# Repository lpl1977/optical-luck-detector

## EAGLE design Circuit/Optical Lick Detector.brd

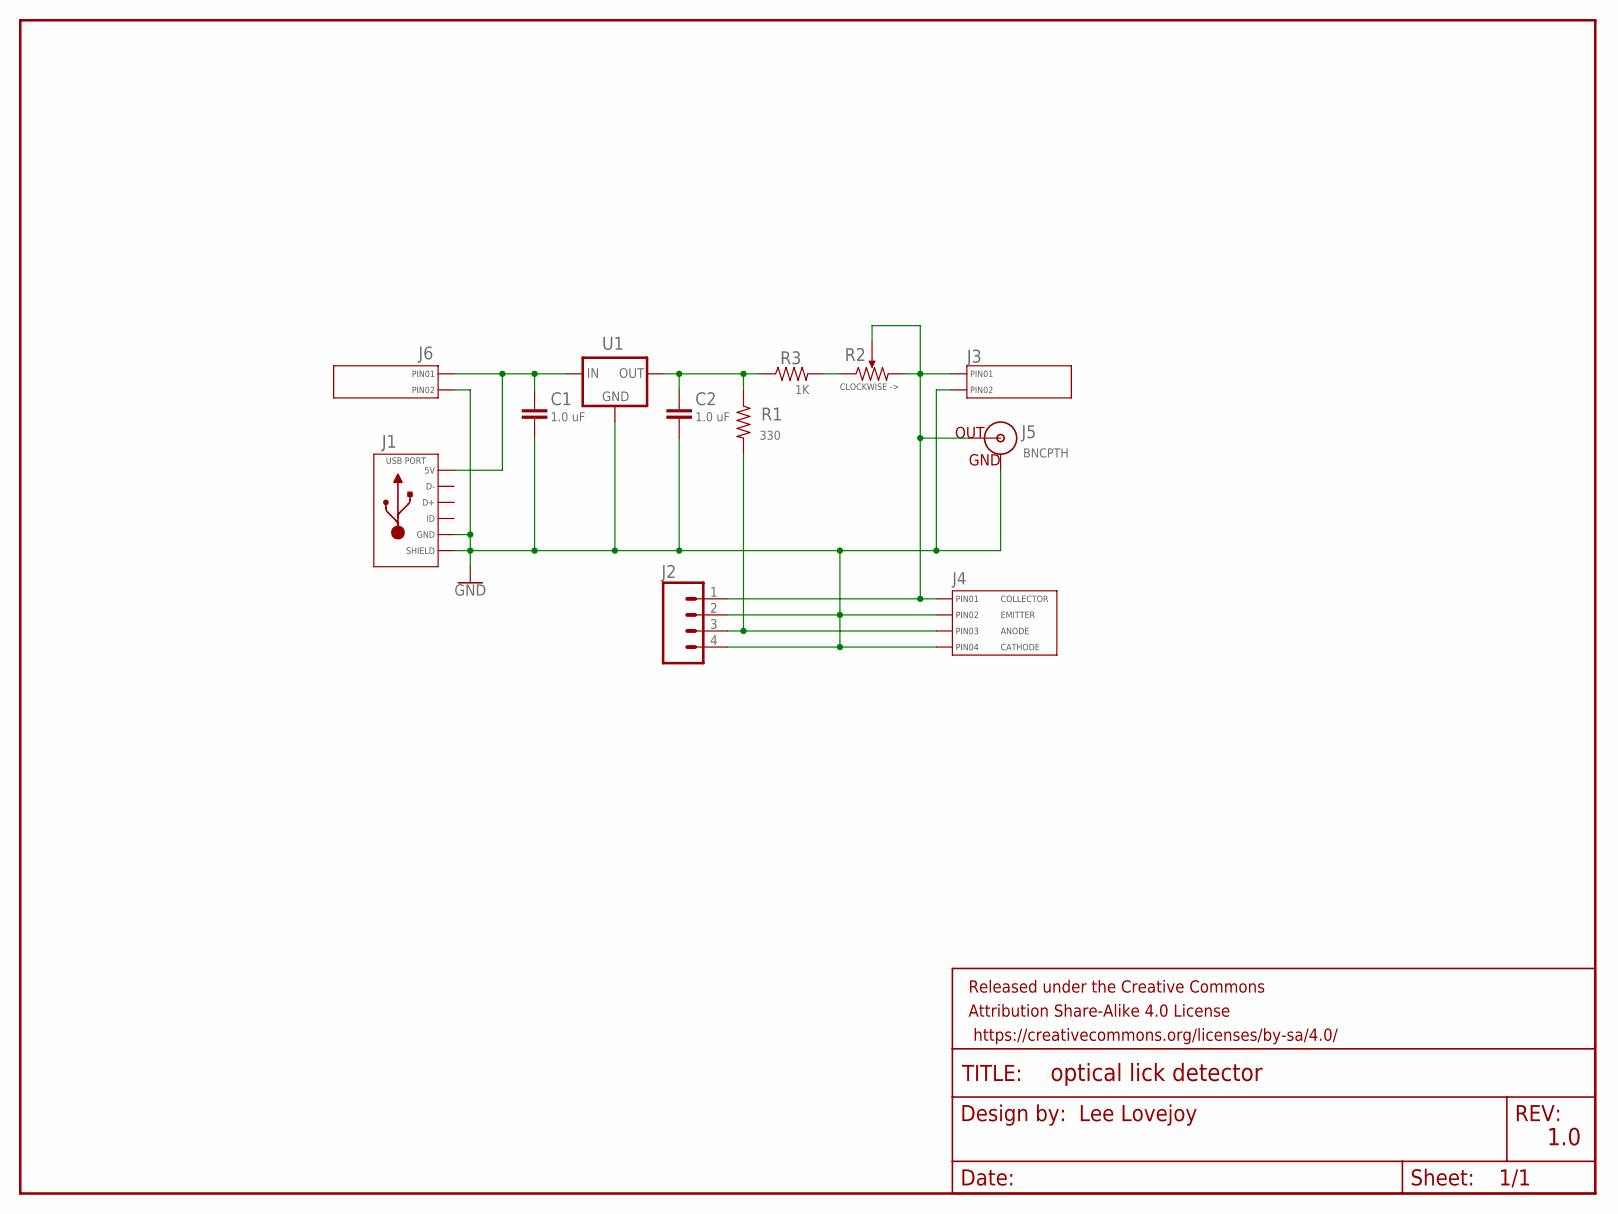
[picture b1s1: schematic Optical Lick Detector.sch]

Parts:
C1, C2: 1.0 uF; C0603
FRAME1: FRAME-LETTER; CREATIVE_COMMONS
J1: MF-CON-MICROUSB-RIGHT; MICROUSB-RIGHT
J2: CONN_041X04_NO_SILK; 1X04_NO_SILK
J3, J6: CONN_023.5MM; SCREWTERMINAL-3.5MM-2
J4: CONN_04SCREW; SCREWTERMINAL-3.5MM-4
J5: BNCPTH; BNC
R1: 330; R0402
R2: MF-RES-TC33X-10K; TC33
R3: 1K; R0402
U1: MIC5200; SOT223

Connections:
ANODE: J2.3, J4.3 (PIN3), R1.P$2
COLLECTOR: J2.1, J3.1 (PIN1), J4.1 (PIN1), J5.S (OUT), R2.P$2, R2.P$3
GND: C1.P$2 (2), C2.P$2 (2), J1.5 (GND), J1.S1 (SLD), J1.S2 (SLD), J1.S3 (SLD), J1.S4 (SLD), J1.S5 (SLD), J1.S6 (SLD), J2.2, J2.4, J3.2 (PIN2), J4.2 (PIN2), J4.4 (PIN4), J5.GND, J6.2 (PIN2), U1.2 (GND), U1.4 (GND)
unnamed: C1.P$1 (1), J1.1 (5V), J6.1 (PIN1), U1.1 (IN)
unnamed: C2.P$1 (1), R1.P$1, R3.P$1, U1.3 (OUT)
unnamed: R2.P$1, R3.P$2

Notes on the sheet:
1.0

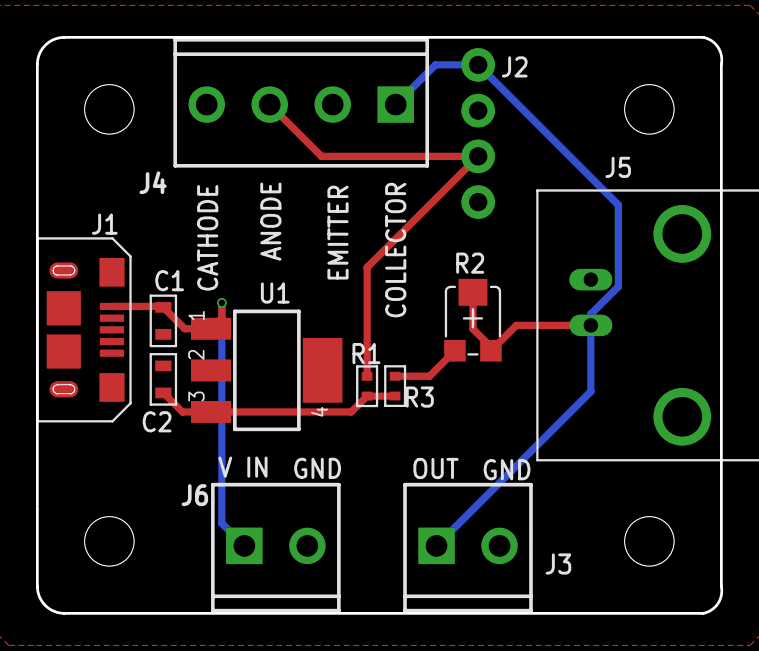
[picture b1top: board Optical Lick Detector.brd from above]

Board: 2 copper layers, 38.0 x 32.0 mm, 13 parts (0 on the bottom side), 6 nets.

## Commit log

2019-05-03 Schematics and board files for optical lick detector
    EAGLE schematics and board files for optical lick detector.
2019-05-17 Rearrange files
    Create separate folders for physical and circuit schematics
2019-05-17 Delete .DS_Store
    obvious reasons

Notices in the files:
parts and their libraries:
Training Doors: Released under the Creative Commons Attribution Share-Alike 4.0 License
Training Doors: https://creativecommons.org/licenses/by-sa/4.0
SparkFun-Connectors: Licensing: Creative Commons ShareAlike 4.0 International - https://creativecommons.org/licenses/by-sa/4.0
